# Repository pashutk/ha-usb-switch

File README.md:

# Homeassistant powered USB power switch

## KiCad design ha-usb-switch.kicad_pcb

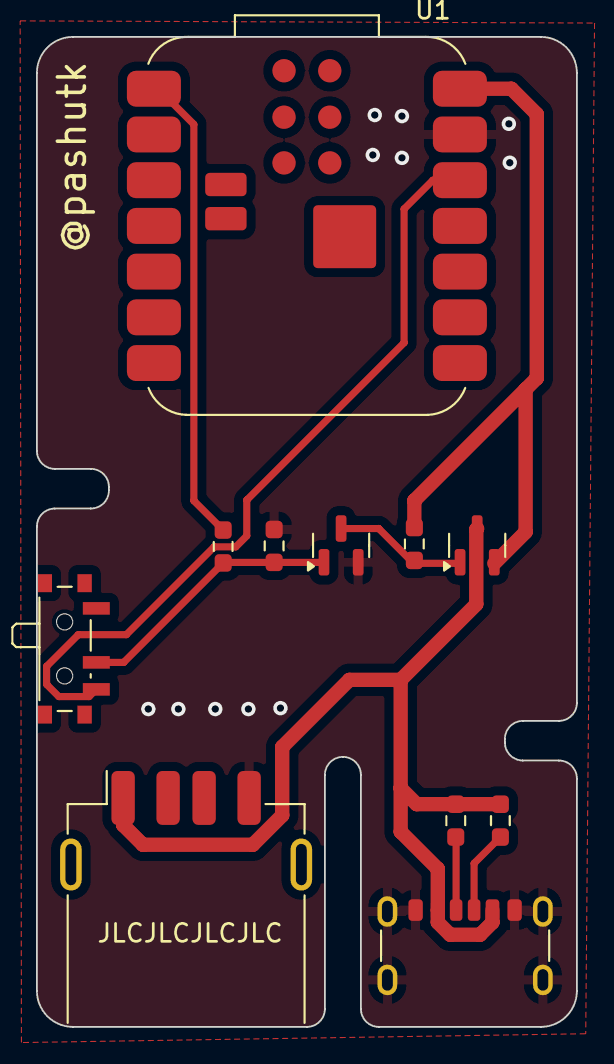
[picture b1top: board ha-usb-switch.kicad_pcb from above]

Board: 2 copper layers, 30.0 x 55.0 mm, 11 parts (0 on the bottom side), 9 nets.

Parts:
J1: USB4125-GF-A-0190_REVA2; USB_C_Receptacle_GCT_USB4125-xx-x-0190_6P_TopMnt_Horizontal
J4: USB1046-XX-XXXX-X-B-X_REVB; USB_A_Receptacle_GCT_USB1046
Q2: AO3401A; SOT-23
Q3: AO3400A; SOT-23
R1: 1k; R_0603_1608Metric_Pad0.98x0.95mm_HandSolder
R2, R3: 10k; R_0603_1608Metric_Pad0.98x0.95mm_HandSolder
R4, R5: 56k; R_0603_1608Metric_Pad0.98x0.95mm_HandSolder
SW2: SW_SPDT; SW_SPDT_PCM12
U1: MOUDLE-SEEEDUINO-XIAO-ESP32C3; MCU_Seeed_ESP32C3

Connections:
+3.3V: SW2.3 (C), U1.12 (3V3)
+5V: J1.A9 (VBUS), J1.B9 (VBUS), J4.1 (VBUS), Q2.3 (D), R4.2, R5.1
CTRL: R1.2, U1.1 (PA02_A0_D0)
GND: J1.A12 (GND), J1.B12 (GND), J1.S1 (SHIELD), J4.4 (GND), Q3.2 (S), R3.2, U1.13 (GND)
unnamed: J1.A5 (CC1), R4.1
unnamed: J1.B5 (CC2), R5.2
unnamed: Q2.1 (G), Q3.3 (D), R2.2
unnamed: Q3.1 (G), R1.1, R3.1, SW2.2 (B)
VBUS: Q2.2 (S), R2.1, U1.14 (5V)

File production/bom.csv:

Designator,Footprint,Quantity,Value,LCSC Part #
J1,USB_C_Receptacle_GCT_USB4125-xx-x-0190_6P_TopMnt_Horizontal,1,USB4125-GF-A-0190_REVA2,
J4,USB_A_Receptacle_GCT_USB1046,1,USB1046-XX-XXXX-X-B-X_REVB,
Q2,SOT-23,1,AO3401A,
Q3,SOT-23,1,AO3400A,
R1,0603,1,1k,
"R2, R3",0603,2,10k,
"R4, R5",0603,2,56k,
SW2,SW_SPDT_PCM12,1,SW_SPDT,
U1,MCU_Seeed_ESP32C3,1,MOUDLE-SEEEDUINO-XIAO-ESP32C3,

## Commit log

2024-09-20 Update schematic plot file
2024-09-20 Update lock files
2024-09-24 Add USB C sink pullups
